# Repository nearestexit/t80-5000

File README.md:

# T80-5000 & T80-5700

[QMK](https://github.com/qmk/qmk_firmware) Compatible Open Hardware USB-C PCBs for the vintage [Cherry G80-5000](https://web.archive.org/web/20250114051116/https://deskthority.net/wiki/Cherry_G80-5000) split ergonomic keyboard and its companion numpad, the G80-5700.

## Overview
The original G80-5000 has two halves which are attached together with a spring, similar to the IBM M15 and the Apple Adjustable Keyboard. They cannot be detached from each other, and the right half must always act as the host.
The original G80-5700 companion numpad can only function when plugged in to the right half of the G80-5000.

This project brings the G80-5000 & 5700 into the 21st century, with all three pieces able to function independently.
There are four PCBs included in this project: the T80-5000 Left, T80-5000 Right, T80-5000 Daughterboard, and T80-5700.
The T80-5000 Left & Right work with QMK's [split keyboard](https://docs.qmk.fm/features/split_keyboard) functionality, and the T80-5700 functions as an independent keyboard which can be passed through the right half's USB hub.

Production files are included for production at [JLCPCB](https://jlcpcb.com/).

## Features
 - USB-C in several configuration options, including internally attached and externally detachable
 - Integrated USB2.0 hub intended for T80-5700 numpad to support passthrough like the original G80-5700
 - [RP2040](https://www.raspberrypi.com/products/rp2040/specifications/) MCU(s) supported by the open-source QMK firmware project

## Supported layouts
 - ISO and ANSI
 - Split backspace
 - 5x4 ortholinear numpad
 - Stepped and centered caps lock

## Configuration options
 - The left and right halves can function independently or in a primary/secondary configuration.
 - The left half's USB-C connector is only accessible internally.
 - The right half's USB-C connector takes advantage of the cutout for the original 5-pin mini DIN to be externally detachable. It is recommended to use the right half as the host.
 - The left and right half can be connected by an internally attached TRRS cable or 4-pin JST-SH cable.
 - The JST-SH cable is small enough to fit through a replacement spring.
 - The daughterboard fits in the right half, leverages the same cutout in the case, and serves as the downstream facing USB-C port for the integrated USB hub. It is connected to the right half with a 4-pin JST-SH cable.
 - The T80-5700 has an internally detachable USB-C connector and functions as an independent USB device.

## JLCPCB Ordering Information
1. On jlcpcb.com, click "order now" and "add gerber file"
2. Navigate to the directory with the gerber.zip - for example, t80-5000-left\jlcpcb\production_files
3. Wait for the gerber to upload.
4. Select the number of PCBs you wish to build.
5. Make sure PCB thickness is set to 1.6mm.
6. Make sure Via covering is set to "tented".
7. Make sure Min via hole size/diameter is set to "0.3mm"
8. For "Mark on PCB" select "Order Number (Specify Position)"
9. Turn the "PCB Assembly" option on
10. Make sure PCBA type is set to "Economic"
11. For "Assembly side", if you are ordering the daughterboard select "top side", otherwise select "bottom side"
12. Click "next", and then "next" again
13. Click "Add BOM File" and select the BOM csv - for example, BOM-T80-5000-left.csv
14. Click "Add CPL File" and select the CPL csv - for example, CPL-T80-5000-left.csv
15. Click "Process BOM and CPL"
16. Make sure all parts are in stock - if any are not in stock, you will need to find replacements
17. If you wish to purchase and solder the TRRS sockets separately (recommended to save money), unselect "J2" in this list
18. **IMPORTANT:** Click "Bottom" to view the bottom side of the PCB, and begin inspecting the component placements. You **WILL** need to correct some component rotations. If you are not sure at this step, do not continue!
19. Click "next" and finish checking out.

When I ordered the V0.1 prototype on 11/8/2024, The total price was $207.63 total for Qty. 5 of all PCBs (left, right, daughterboard, and 5700) plus shipping, or roughly $52.71 per set of Left, Right, Daughterboard, and 5700.

## Additional Components:
- 1x 1:1 ~50mm 4-pin JST-SH cable to connect Left PCB to daughterboard
  - **IMPORTANT:** this must be a 1:1 cable, or else you will short VCC to ground!
  - This means that pin 1 of one connector must be wired to pin 1 of the other connector. If you are unsure, lay the cable flat with no wires crossing - if the connectors on either side are the same way up, it is NOT a 1:1 cable. If they are flipped, it is a 1:1 cable.
  - You can get 1:1 JST-SH cables from many places, but I recommend purchasing a Sparkfun QWIIC starter kit like [this](https://www.amazon.com/dp/B08HQ1VSVL)
- 1x 1:1 ~300mm 4-pin JST-SH cable **OR** TRRS cable to connect Left PCB to Right PCB
  - **IMPORTANT:** do not hotswap these connectors! Plugging or unplugging the TRRS connector with power on will short VCC to ground and potentially damage the MCU.
- 3x LEDs for lock lights
  - The board comes with 300 ohm 1206 package resistors pre-soldered. There are holes to add through-hole resistors if you want to change the resistance.
- ~113 MX-compatible switches (this will vary depending on the layout you choose - my ISO configuration uses 108 switches)
- [PJ-320A](https://www.lcsc.com/product-detail/Audio-Connectors_XKB-Connectivity-PJ-320A_C2884926.html) 3.5mm 4 pin TRRS receptacle (optional) - if you wish to use a TRRS cable and choose not to have it soldered by JLCPCB
- Spring (optional) - An image displaying the approximate measurements of the original spring is included in the documentation folder. I used [these](https://www.amazon.com/dp/B0BRHF1DBL) springs.

## Firmware
- [Vial-QMK](https://get.vial.today/) .uf2 files are provided in the firmware folder.
- To put the keyboard into bootloader mode to flash the firmware:
1. Unplug the USB cable
2. Short the BOOT pins with a pair of tweezers
3. Plug the USB cable in
4. Stop shorting the BOOT pins.
- The RP2040 will then be loaded onto your computer as a USB storage device. Drag in the .uf2 firmware file, and it will reboot.
- The boot pins can be found on the Left side by removing the 1 key, the Right side by removing the 0 key, and the Numpad by removing the * key.
- Once you have flashed the firmware, you can change the keymap from [vial.rocks](https://vial.rocks)

## Other Important Notes
- The components are soldered on to the bottom of this PCB. If you are not careful when putting the keyboard together, you can knock components off the PCB.
- The USB-C receptacles for the right half and the downstream-facing USB hub are close enough together that if the downstream USB-C port is used, cables with thick ends will not work.
- If you do not use the downstream-facing USB-C port, there is no limit to the size of the USB-C cable.
- The USB-Hub will not function if the left side is used as the host.

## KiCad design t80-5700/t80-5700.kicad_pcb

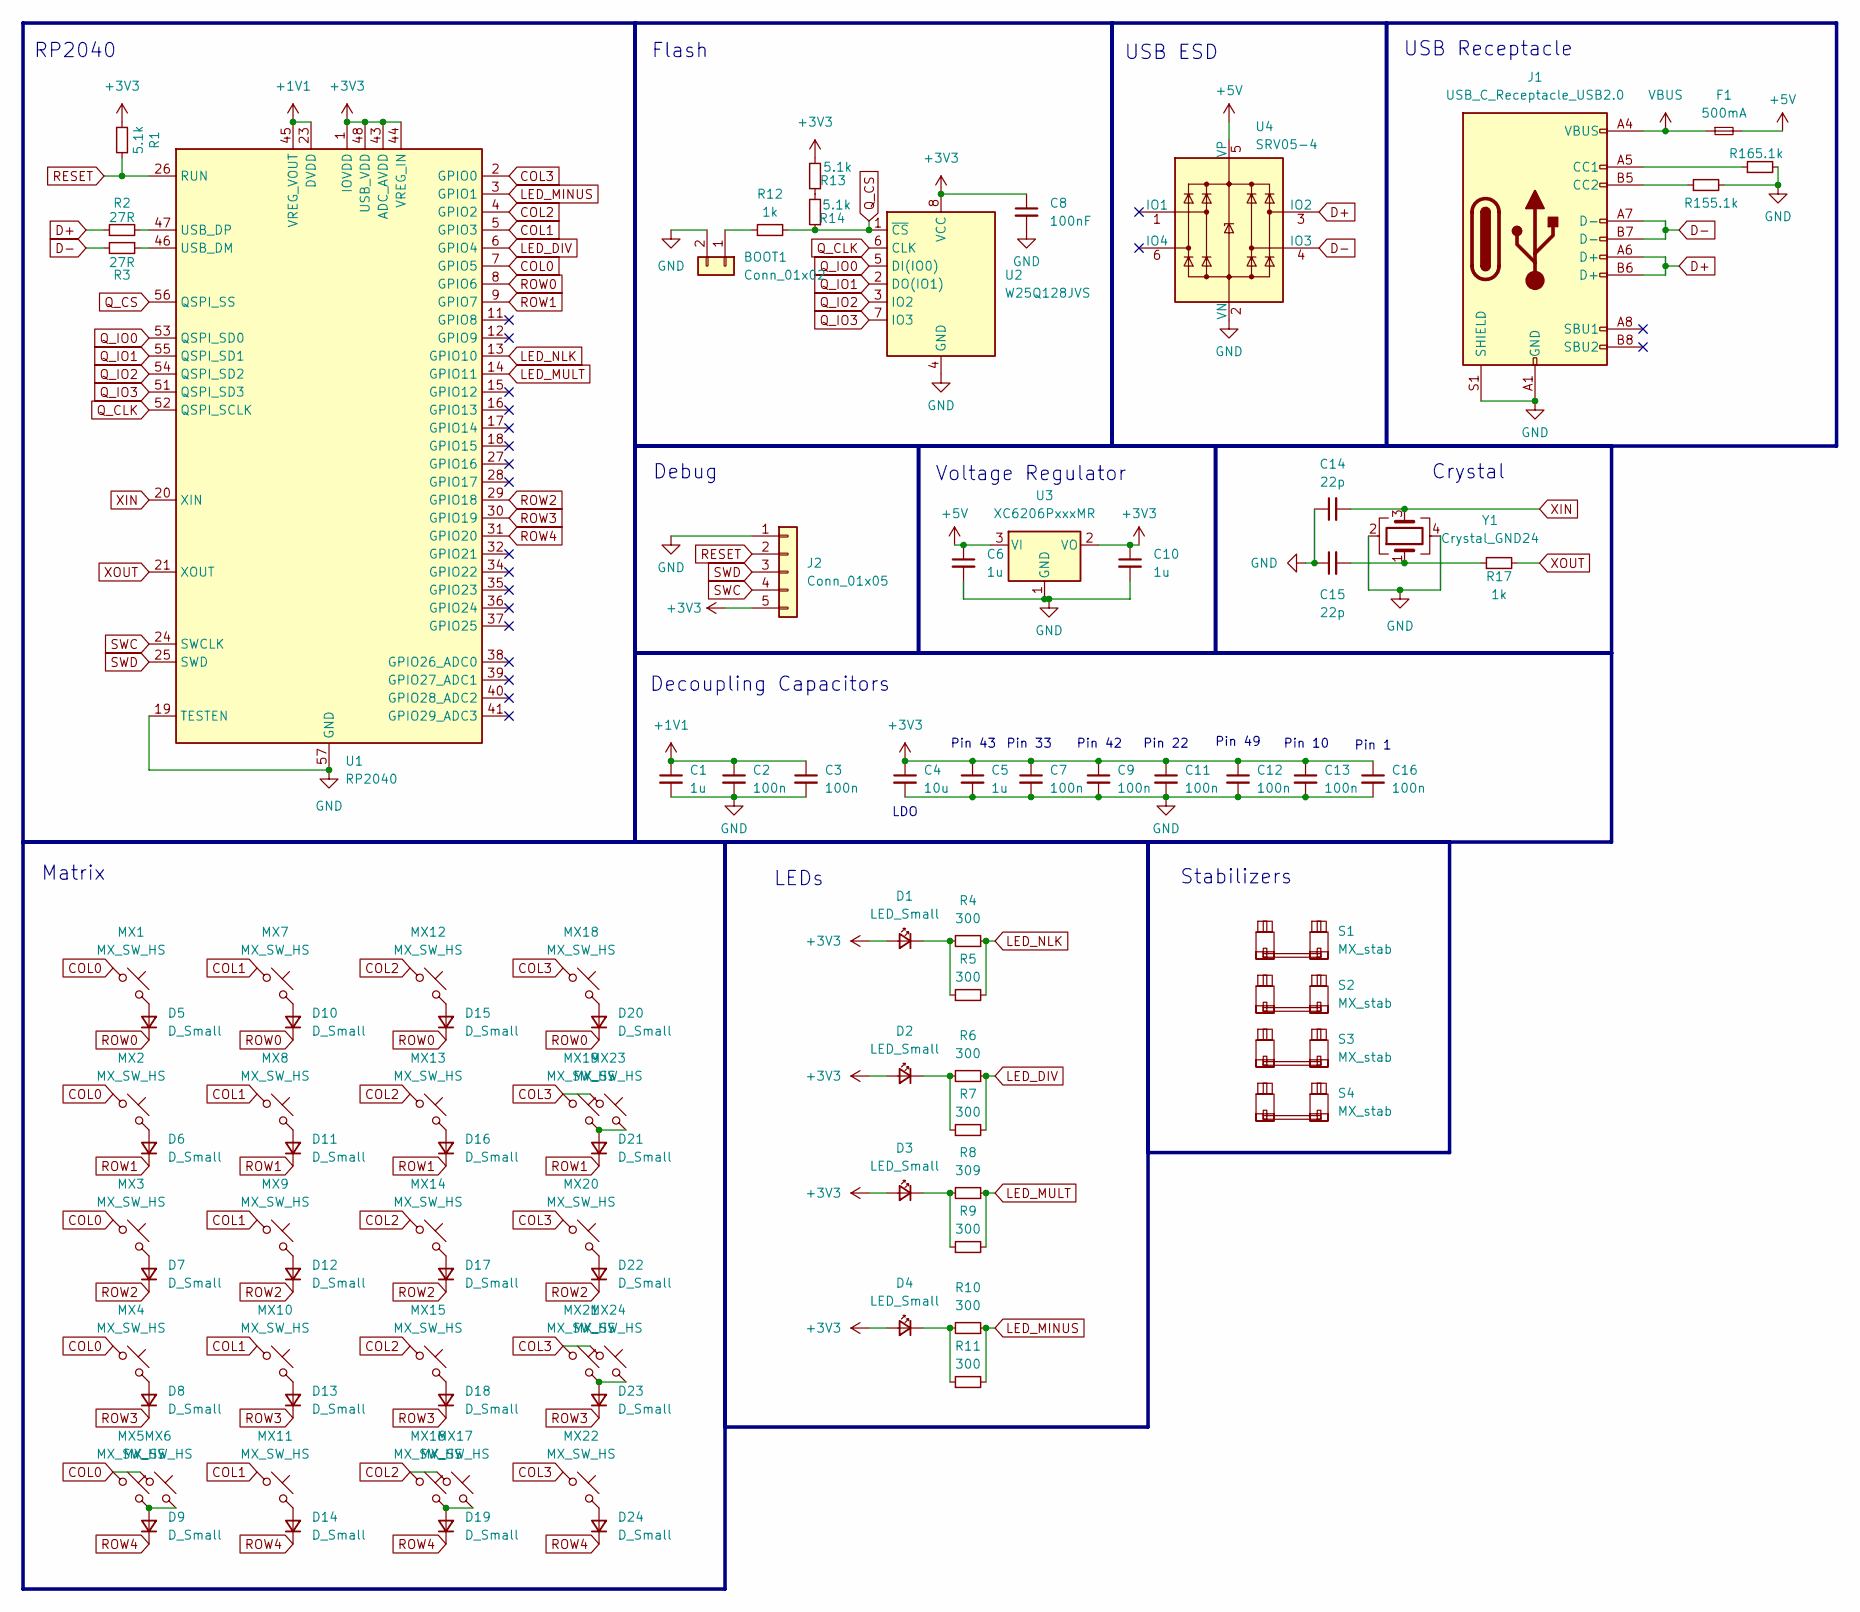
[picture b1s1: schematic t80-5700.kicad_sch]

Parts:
BOOT1: Conn_01x02; PinHeader_1x02_P2.54mm_Vertical
C1, C5, C6, C10: 1u; C_0402_1005Metric
C2, C3, C7, C9, C11, C12, C13, C16: 100n; C_0402_1005Metric
C4: 10u; C_0603_1608Metric
C8: 100nF; C_0402_1005Metric
C14, C15: 22p; C_0402_1005Metric
D1, D2, D3, D4: LED_Small; LED_MX_3mm
D5, D6, D7, D8, D9, D10, D11, D12, D13, D14, D15, D16, D17, D18, D19, D20, D21, D22, D23, D24: D_Small; D_SOD-123-ShiftedSoldermask
F1: 500mA; Fuse_1206_3216Metric
J1: USB_C_Receptacle_USB2.0; USB_C_Receptacle_HRO_TYPE-C-31-M-12
J2: Conn_01x05; PinHeader_1x05_P2.54mm_Vertical
MX1, MX2, MX3, MX4, MX5, MX6, MX7, MX8, MX9, MX10, MX11, MX12, MX13, MX14, MX15, MX16, MX17, MX18, MX19, MX20, MX21, MX22, MX23, MX24: MX_SW_HS; SW_MX_1u
R1: 5.1k; R_0603_1608Metric
R2, R3: 27R; R_0402_1005Metric
R4, R6, R10: 300; R_Axial_DIN0207_L6.3mm_D2.5mm_P10.16mm_Horizontal
R5, R7, R9, R11: 300; R_1206_3216Metric_Pad1.30x1.75mm_HandSolder
R8: 309; R_Axial_DIN0207_L6.3mm_D2.5mm_P10.16mm_Horizontal
R12: 1k; R_0603_1608Metric
R13, R14, R15, R16: 5.1k; R_0402_1005Metric
R17: 1k; R_0402_1005Metric
S1, S2, S3, S4: MX_stab; STAB_MX_P_2u
U1: RP2040; QFN-56-1EP_7x7mm_P0.4mm_EP3.2x3.2mm
U2: W25Q128JVS; SOIC-8_5.23x5.23mm_P1.27mm
U3: XC6206PxxxMR; SOT-23-3
U4: SRV05-4; SOT-23-6-routable
Y1: Crystal_GND24; Crystal_SMD_3225-4Pin_3.2x2.5mm

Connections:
+1V1: C1.1, C2.1, C3.1, U1.23 (DVDD), U1.45 (VREG_VOUT), U1.50 (DVDD)
+3V3: C4.1, C5.1, C7.1, C8.1, C9.1, C10.1, C11.1, C12.1, C13.1, C16.1, D1.2 (A), D2.2 (A), D3.2 (A), D4.2 (A), J2.5, R1.2, R13.2, U1.1 (IOVDD), U1.10 (IOVDD), U1.22 (IOVDD), U1.33 (IOVDD), U1.42 (IOVDD), U1.43 (ADC_AVDD), U1.44 (VREG_IN), U1.48 (USB_VDD), U1.49 (IOVDD), U2.8 (VCC), U3.2 (VO)
+5V: C6.1, F1.2, U3.3 (VI), U4.5 (VP)
COL0: MX1.1, MX2.1, MX3.1, MX4.1, MX5.1, MX6.1, U1.7 (GPIO5)
COL1: MX7.1, MX8.1, MX9.1, MX10.1, MX11.1, U1.5 (GPIO3)
COL2: MX12.1, MX13.1, MX14.1, MX15.1, MX16.1, MX17.1, U1.4 (GPIO2)
COL3: MX18.1, MX19.1, MX20.1, MX21.1, MX22.1, MX23.1, MX24.1, U1.2 (GPIO0)
D+: J1.A6 (D+), J1.B6 (D+), R2.1, U4.3 (IO2)
D-: J1.A7 (D-), J1.B7 (D-), R3.2, U4.4 (IO3)
GND: BOOT1.2, C1.2, C2.2, C3.2, C4.2, C5.2, C6.2, C7.2, C8.2, C9.2, C10.2, C11.2, C12.2, C13.2, C14.1, C15.1, C16.2, J1.A1 (GND), J1.A12 (GND), J1.B1 (GND), J1.B12 (GND), J1.S1 (SHIELD), J2.1, R15.2, R16.2, U1.19 (TESTEN), U1.57 (GND), U2.4 (GND), U3.1 (GND), U4.2 (VN), Y1.2, Y1.4
LED_DIV: R6.1, R7.2, U1.6 (GPIO4)
LED_MINUS: R10.1, R11.2, U1.3 (GPIO1)
LED_MULT: R8.1, R9.2, U1.14 (GPIO11)
LED_NLK: R4.1, R5.2, U1.13 (GPIO10)
unnamed: BOOT1.1, R12.1
unnamed: C15.2, R17.1, Y1.1
unnamed: D1.1 (K), R4.2, R5.1
unnamed: D2.1 (K), R6.2, R7.1
unnamed: D3.1 (K), R8.2, R9.1
unnamed: D4.1 (K), R10.2, R11.1
unnamed: D5.2 (A), MX1.2
unnamed: D6.2 (A), MX2.2
unnamed: D7.2 (A), MX3.2
unnamed: D8.2 (A), MX4.2
unnamed: D9.2 (A), MX5.2, MX6.2
unnamed: D10.2 (A), MX7.2
unnamed: D11.2 (A), MX8.2
unnamed: D12.2 (A), MX9.2
unnamed: D13.2 (A), MX10.2
unnamed: D14.2 (A), MX11.2
unnamed: D15.2 (A), MX12.2
unnamed: D16.2 (A), MX13.2
unnamed: D17.2 (A), MX14.2
unnamed: D18.2 (A), MX15.2
unnamed: D19.2 (A), MX16.2, MX17.2
unnamed: D20.2 (A), MX18.2
unnamed: D21.2 (A), MX19.2, MX23.2
unnamed: D22.2 (A), MX20.2
unnamed: D23.2 (A), MX21.2, MX24.2
unnamed: D24.2 (A), MX22.2
unnamed: J1.A5 (CC1), R16.1
unnamed: J1.B5 (CC2), R15.1
unnamed: R13.1, R14.2
unnamed: R3.1, U1.46 (USB_DM)
unnamed: R2.2, U1.47 (USB_DP)
Q_CLK: U1.52 (QSPI_SCLK), U2.6 (CLK)
Q_CS: R12.2, R14.1, U1.56 (QSPI_SS), U2.1 (~CS)
Q_IO0: U1.53 (QSPI_SD0), U2.5 (DI(IO0))
Q_IO1: U1.55 (QSPI_SD1), U2.2 (DO(IO1))
Q_IO2: U1.54 (QSPI_SD2), U2.3 (IO2)
Q_IO3: U1.51 (QSPI_SD3), U2.7 (IO3)
RESET: J2.2, R1.1, U1.26 (RUN)
ROW0: D5.1 (K), D10.1 (K), D15.1 (K), D20.1 (K), U1.8 (GPIO6)
ROW1: D6.1 (K), D11.1 (K), D16.1 (K), D21.1 (K), U1.9 (GPIO7)
ROW2: D7.1 (K), D12.1 (K), D17.1 (K), D22.1 (K), U1.29 (GPIO18)
ROW3: D8.1 (K), D13.1 (K), D18.1 (K), D23.1 (K), U1.30 (GPIO19)
ROW4: D9.1 (K), D14.1 (K), D19.1 (K), D24.1 (K), U1.31 (GPIO20)
SWC: J2.4, U1.24 (SWCLK)
SWD: J2.3, U1.25 (SWD)
VBUS: F1.1, J1.A4 (VBUS), J1.A9 (VBUS), J1.B4 (VBUS), J1.B9 (VBUS)
XIN: C14.2, U1.20 (XIN), Y1.3
XOUT: R17.2, U1.21 (XOUT)

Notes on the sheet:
Pin 43
LDO
USB ESD
Stabilizers
Crystal
Pin 1
USB Receptacle
Pin 33
Pin 49
Debug
LEDs
Pin 10
Decoupling Capacitors
Flash
Pin 42
RP2040
Voltage Regulator
Matrix
Pin 22

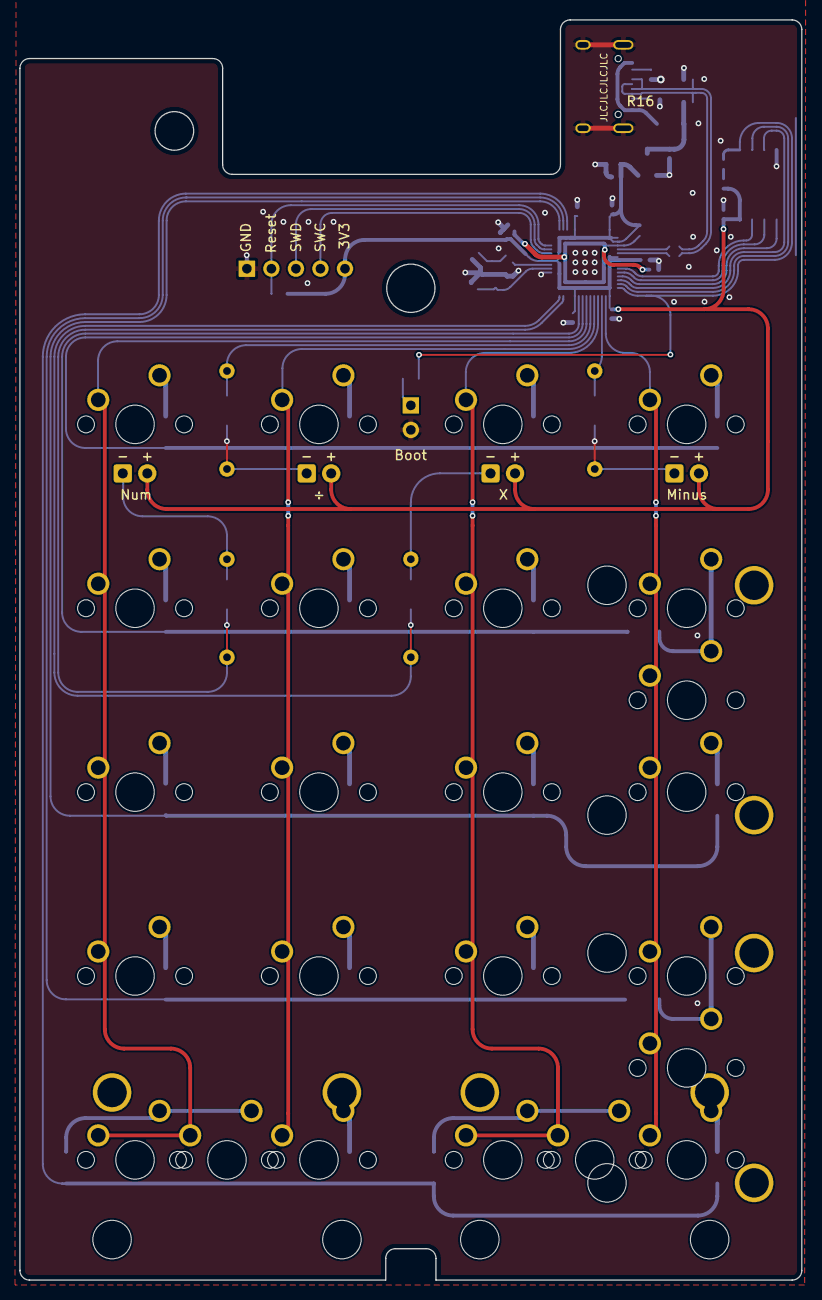
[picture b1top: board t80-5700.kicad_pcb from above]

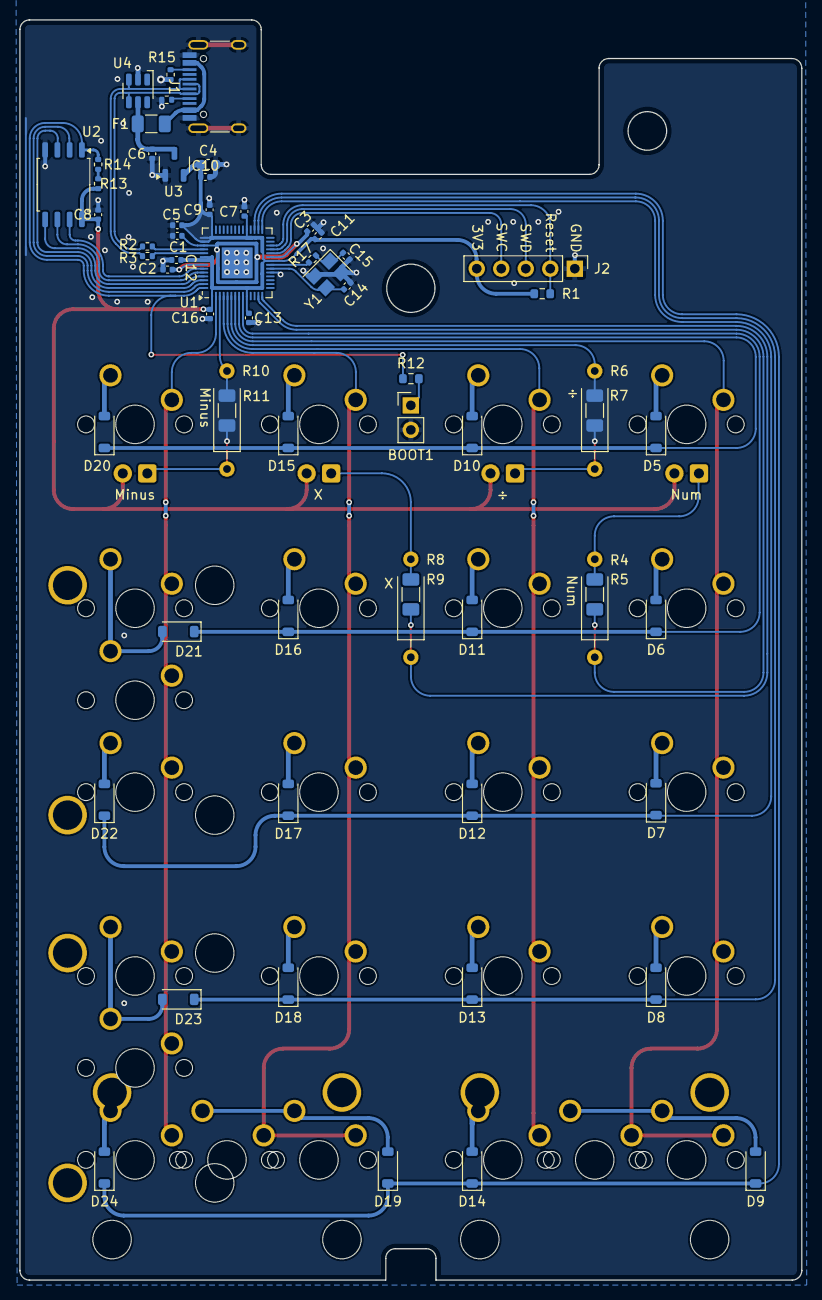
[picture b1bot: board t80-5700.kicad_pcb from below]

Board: 2 copper layers, 81.0 x 130.6 mm, 94 parts (70 on the bottom side), 61 nets.

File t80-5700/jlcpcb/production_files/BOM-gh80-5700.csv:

Comment,Designator,Footprint,LCSC,Quantity
1k,R17,R_0402_1005Metric,C11702,1
W25Q128JVS,U2,SOIC-8_5.23x5.23mm_P1.27mm,C131025,1
27R,"R2,R3",R_0402_1005Metric,C138021,2
22p,"C14,C15",C_0402_1005Metric,C1555,2
USB_C_Receptacle_USB2.0,J1,USB_C_Receptacle_HRO_TYPE-C-31-M-12,C165948,1
300,"R11,R5,R7,R9",R_1206_3216Metric_Pad1.30x1.75mm_HandSolder,C17887,4
10u,C4,C_0603_1608Metric,C19702,1
RP2040,U1,QFN-56-1EP_7x7mm_P0.4mm_EP3.2x3.2mm,C2040,1
1k,R12,R_0603_1608Metric,C21190,1
5.1k,R1,R_0603_1608Metric,C23186,1
5.1k,"R13,R14,R15,R16",R_0402_1005Metric,C25905,4
100n,"C11,C12,C13,C16,C2,C3,C7,C8,C9",C_0402_1005Metric,C307331,9
1u,"C1,C10,C5,C6",C_0402_1005Metric,C52923,4
XC6206PxxxMR,U3,SOT-23-3,C5446,1
500mA,F1,Fuse_1206_3216Metric,C70076,1
D_Small,"D10,D11,D12,D13,D14,D15,D16,D17,D18,D19,D20,D21,D22,D23,D24,D5,D6,D7,D8,D9",D_SOD-123-ShiftedSoldermask,C81598,20
SRV05-4,U4,SOT-23-6-routable,C85364,1
Crystal_GND24,Y1,Crystal_SMD_3225-4Pin_3.2x2.5mm,C9002,1

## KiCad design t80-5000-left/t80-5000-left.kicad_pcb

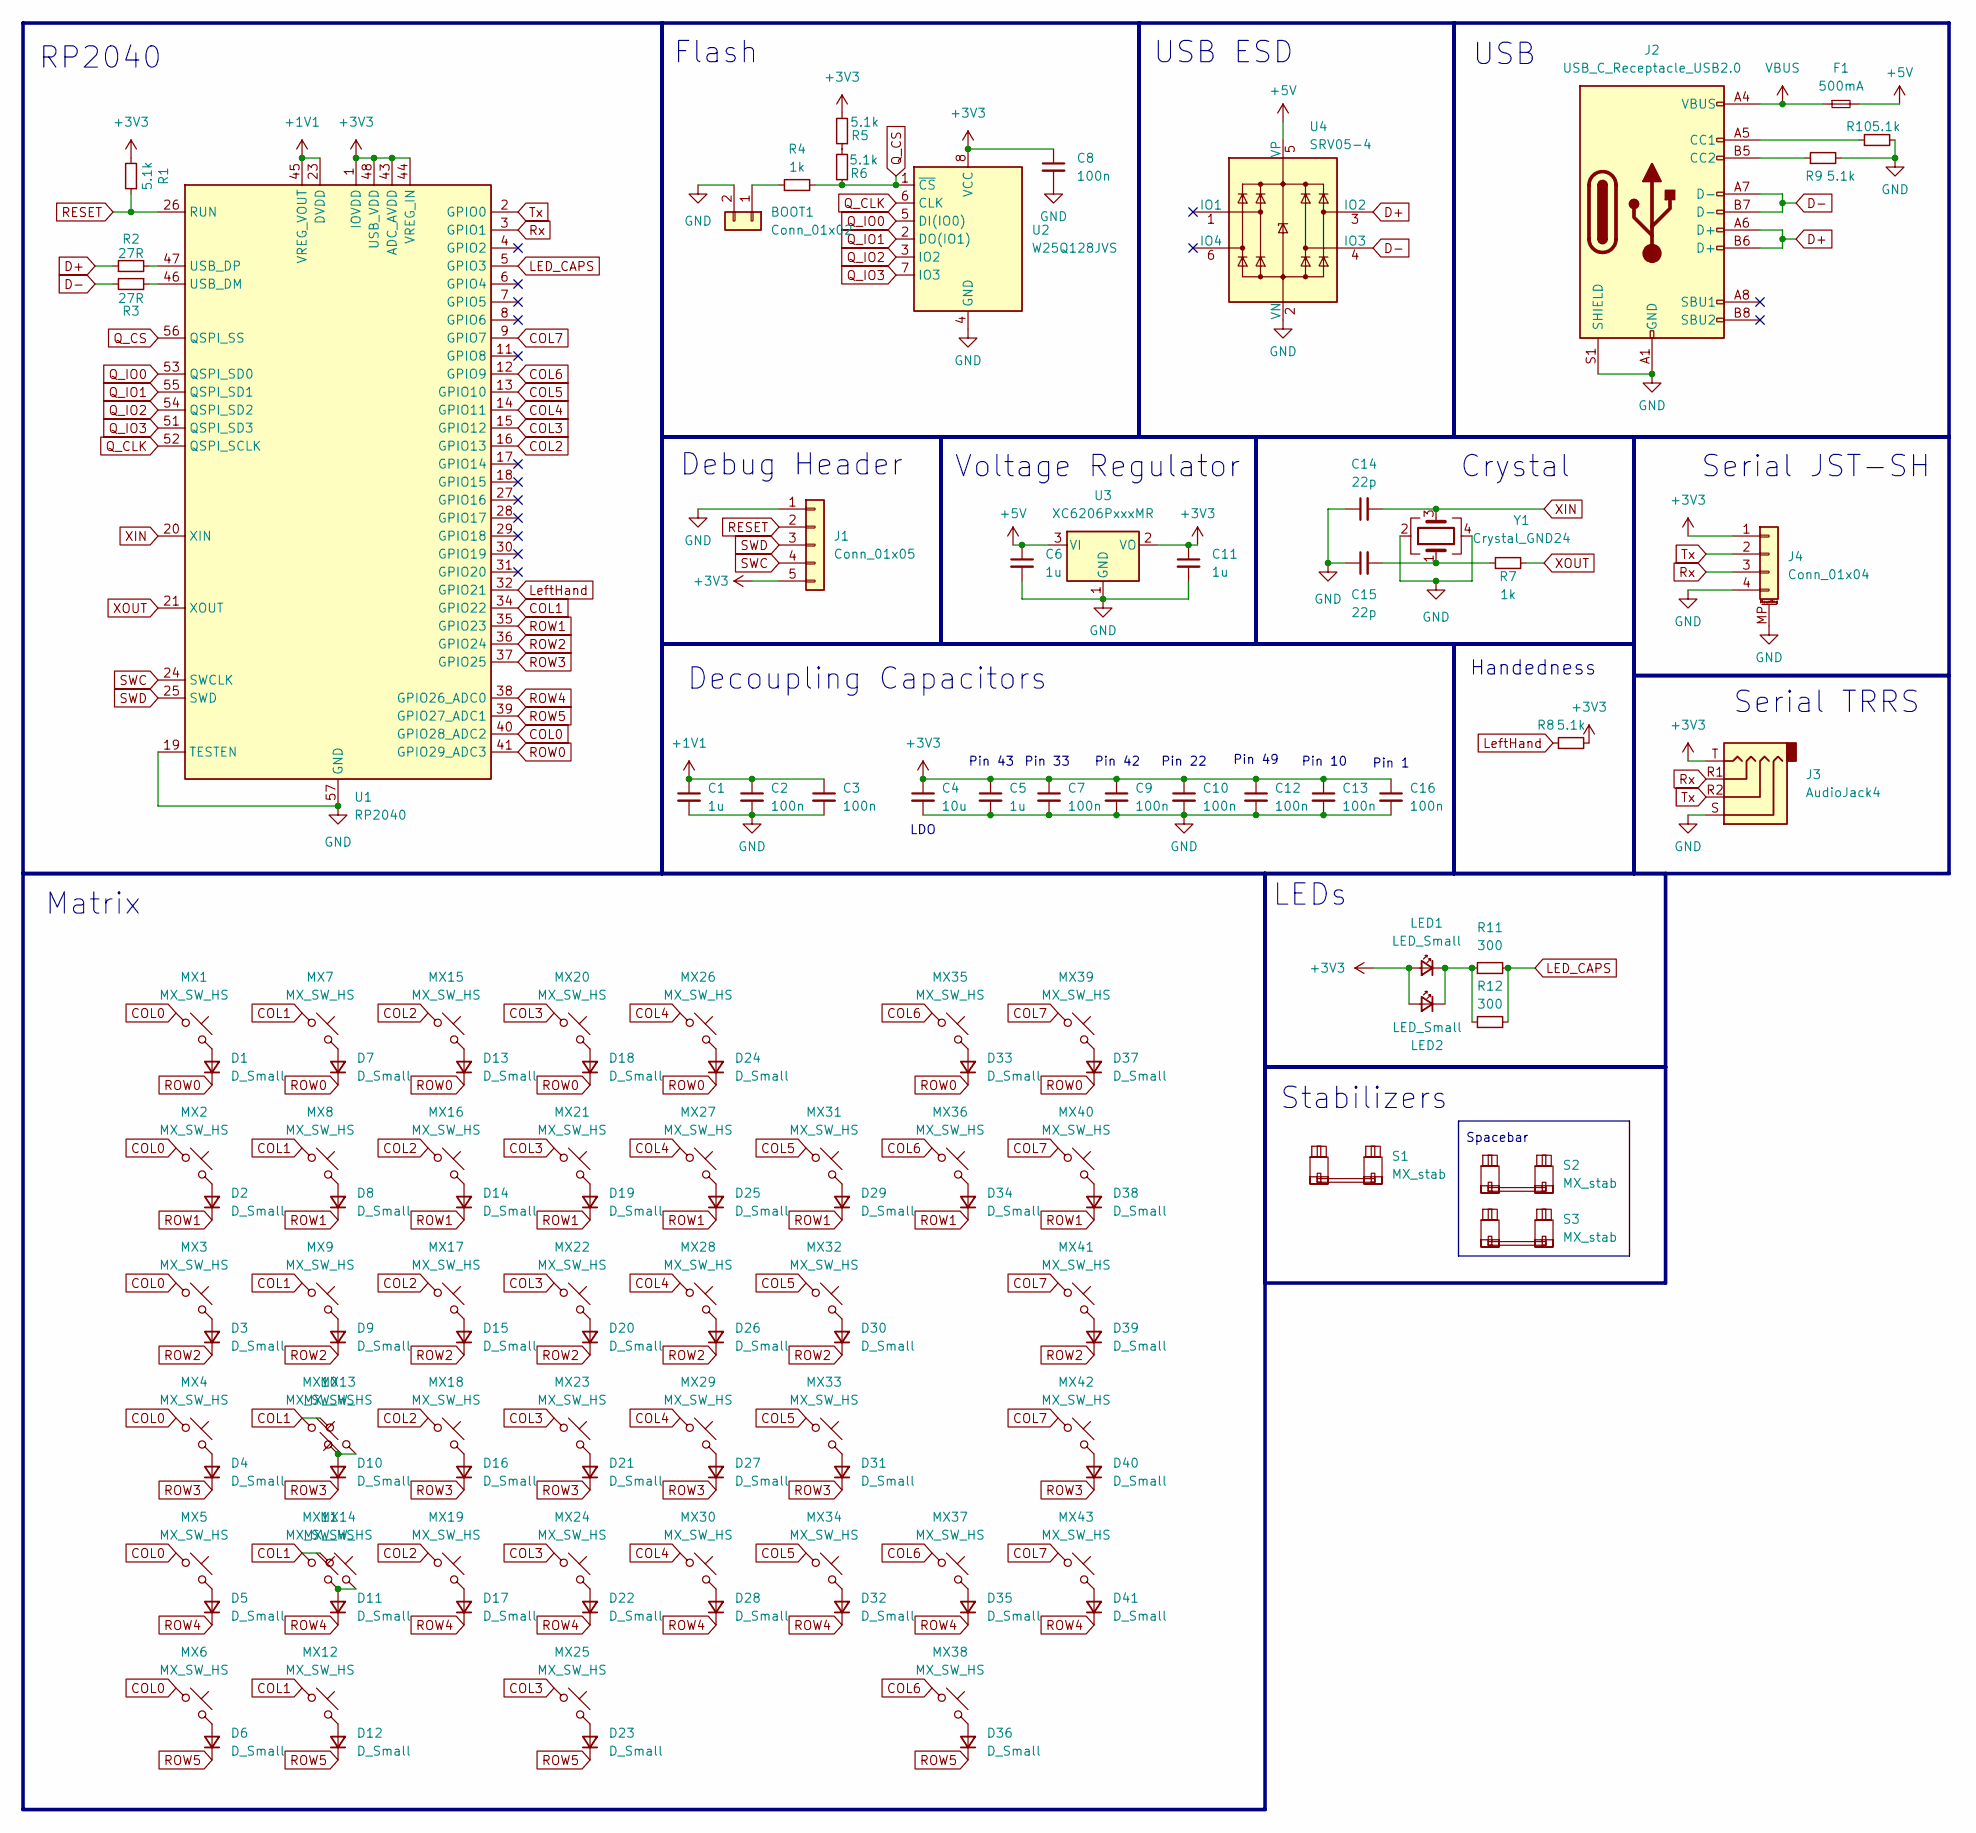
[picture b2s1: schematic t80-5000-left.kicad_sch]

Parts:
BOOT1: Conn_01x02; PinHeader_1x02_P2.54mm_Vertical
C1, C5, C6, C11: 1u; C_0402_1005Metric
C2, C3, C7, C8, C9, C10, C12, C13, C16: 100n; C_0402_1005Metric
C4: 10u; C_0603_1608Metric
C14, C15: 22p; C_0402_1005Metric
D1, D2, D3, D4, D5, D6, D7, D8, D9, D10, D11, D12, D13, D14, D15, D16, D17, D18, D19, D20, D21, D22, D23, D24, D25, D26, D27, D28, D29, D30, D31, D32, D33, D34, D35, D36, D37, D38, D39, D40, D41: D_Small; D_SOD-123-ShiftedSoldermask
F1: 500mA; Fuse_1206_3216Metric
J1: Conn_01x05; PinHeader_1x05_P2.54mm_Vertical
J2: USB_C_Receptacle_USB2.0; USB_C_Receptacle_HRO_TYPE-C-31-M-12
J3: AudioJack4; AUDIO-TH_XKB_PJ-320A
J4: Conn_01x04; JST_SH_SM04B-SRSS-TB_1x04-1MP_P1.00mm_Horizontal
LED1, LED2: LED_Small; LED_MX_3mm
MX1, MX2, MX3, MX4, MX5, MX6, MX7, MX8, MX9, MX10, MX11, MX12, MX13, MX14, MX15, MX16, MX17, MX18, MX19, MX20, MX21, MX22, MX23, MX24, MX25, MX26, MX27, MX28, MX29, MX30, MX31, MX32, MX33, MX34, MX35, MX36, MX37, MX38, MX39, MX40, MX41, MX42, MX43: MX_SW_HS; SW_MX_1u
R1, R5, R6, R9, R10: 5.1k; R_0402_1005Metric
R2, R3: 27R; R_0402_1005Metric
R4, R7: 1k; R_0402_1005Metric
R8: 5.1k; R_0603_1608Metric_Pad0.98x0.95mm_HandSolder
R11: 300; R_Axial_DIN0207_L6.3mm_D2.5mm_P10.16mm_Horizontal
R12: 300; R_1206_3216Metric_Pad1.30x1.75mm_HandSolder
S1: MX_stab; STAB_MX_P_2u
S2: MX_stab; STAB_MX_3.5u_5000
S3: MX_stab; STAB_MX_5000
U1: RP2040; QFN-56-1EP_7x7mm_P0.4mm_EP3.2x3.2mm
U2: W25Q128JVS; SOIC-8_5.23x5.23mm_P1.27mm
U3: XC6206PxxxMR; SOT-23-3
U4: SRV05-4; SOT-23-6-routable
Y1: Crystal_GND24; Crystal_SMD_3225-4Pin_3.2x2.5mm

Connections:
+1V1: C1.1, C2.1, C3.1, U1.23 (DVDD), U1.45 (VREG_VOUT), U1.50 (DVDD)
+3V3: C4.1, C5.1, C7.1, C8.1, C9.1, C10.1, C11.1, C12.1, C13.1, C16.1, J1.5, J3.T, J4.1, LED1.2 (A), LED2.2 (A), R1.2, R5.2, R8.2, U1.1 (IOVDD), U1.10 (IOVDD), U1.22 (IOVDD), U1.33 (IOVDD), U1.42 (IOVDD), U1.43 (ADC_AVDD), U1.44 (VREG_IN), U1.48 (USB_VDD), U1.49 (IOVDD), U2.8 (VCC), U3.2 (VO)
+5V: C6.1, F1.2, U3.3 (VI), U4.5 (VP)
COL0: MX1.1, MX2.1, MX3.1, MX4.1, MX5.1, MX6.1, U1.40 (GPIO28_ADC2)
COL1: MX7.1, MX8.1, MX9.1, MX10.1, MX11.1, MX12.1, MX13.2, MX14.1, U1.34 (GPIO22)
COL2: MX15.1, MX16.1, MX17.1, MX18.1, MX19.1, U1.16 (GPIO13)
COL3: MX20.1, MX21.1, MX22.1, MX23.1, MX24.1, MX25.1, U1.15 (GPIO12)
COL4: MX26.1, MX27.1, MX28.1, MX29.1, MX30.1, U1.14 (GPIO11)
COL5: MX31.1, MX32.1, MX33.1, MX34.1, U1.13 (GPIO10)
COL6: MX35.1, MX36.1, MX37.1, MX38.1, U1.12 (GPIO9)
COL7: MX39.1, MX40.1, MX41.1, MX42.1, MX43.1, U1.9 (GPIO7)
D+: J2.A6 (D+), J2.B6 (D+), R2.1, U4.3 (IO2)
D-: J2.A7 (D-), J2.B7 (D-), R3.2, U4.4 (IO3)
GND: BOOT1.2, C1.2, C2.2, C3.2, C4.2, C5.2, C6.2, C7.2, C8.2, C9.2, C10.2, C11.2, C12.2, C13.2, C14.1, C15.1, C16.2, J1.1, J2.A1 (GND), J2.A12 (GND), J2.B1 (GND), J2.B12 (GND), J2.S1 (SHIELD), J3.S, J4.4, J4.MP (MountPin), R9.2, R10.2, U1.19 (TESTEN), U1.57 (GND), U2.4 (GND), U3.1 (GND), U4.2 (VN), Y1.2, Y1.4
LED_CAPS: R11.2, R12.2, U1.5 (GPIO3)
LeftHand: R8.1, U1.32 (GPIO21)
unnamed: BOOT1.1, R4.1
unnamed: C15.2, R7.1, Y1.1
unnamed: D1.2 (A), MX1.2
unnamed: D2.2 (A), MX2.2
unnamed: D3.2 (A), MX3.2
unnamed: D4.2 (A), MX4.2
unnamed: D5.2 (A), MX5.2
unnamed: D6.2 (A), MX6.2
unnamed: D7.2 (A), MX7.2
unnamed: D8.2 (A), MX8.2
unnamed: D9.2 (A), MX9.2
unnamed: D10.2 (A), MX10.2, MX13.1
unnamed: D11.2 (A), MX11.2, MX14.2
unnamed: D12.2 (A), MX12.2
unnamed: D13.2 (A), MX15.2
unnamed: D14.2 (A), MX16.2
unnamed: D15.2 (A), MX17.2
unnamed: D16.2 (A), MX18.2
unnamed: D17.2 (A), MX19.2
unnamed: D18.2 (A), MX20.2
unnamed: D19.2 (A), MX21.2
unnamed: D20.2 (A), MX22.2
unnamed: D21.2 (A), MX23.2
unnamed: D22.2 (A), MX24.2
unnamed: D23.2 (A), MX25.2
unnamed: D24.2 (A), MX26.2
unnamed: D25.2 (A), MX27.2
unnamed: D26.2 (A), MX28.2
unnamed: D27.2 (A), MX29.2
unnamed: D28.2 (A), MX30.2
unnamed: D29.2 (A), MX31.2
unnamed: D30.2 (A), MX32.2
unnamed: D31.2 (A), MX33.2
unnamed: D32.2 (A), MX34.2
unnamed: D33.2 (A), MX35.2
unnamed: D34.2 (A), MX36.2
unnamed: D35.2 (A), MX37.2
unnamed: D36.2 (A), MX38.2
unnamed: D37.2 (A), MX39.2
unnamed: D38.2 (A), MX40.2
unnamed: D39.2 (A), MX41.2
unnamed: D40.2 (A), MX42.2
unnamed: D41.2 (A), MX43.2
unnamed: J2.A5 (CC1), R10.1
unnamed: J2.B5 (CC2), R9.1
unnamed: LED1.1 (K), LED2.1 (K), R11.1, R12.1
unnamed: R5.1, R6.2
unnamed: R3.1, U1.46 (USB_DM)
unnamed: R2.2, U1.47 (USB_DP)
Q_CLK: U1.52 (QSPI_SCLK), U2.6 (CLK)
Q_CS: R4.2, R6.1, U1.56 (QSPI_SS), U2.1 (~CS)
Q_IO0: U1.53 (QSPI_SD0), U2.5 (DI(IO0))
Q_IO1: U1.55 (QSPI_SD1), U2.2 (DO(IO1))
Q_IO2: U1.54 (QSPI_SD2), U2.3 (IO2)
Q_IO3: U1.51 (QSPI_SD3), U2.7 (IO3)
RESET: J1.2, R1.1, U1.26 (RUN)
ROW0: D1.1 (K), D7.1 (K), D13.1 (K), D18.1 (K), D24.1 (K), D33.1 (K), D37.1 (K), U1.41 (GPIO29_ADC3)
ROW1: D2.1 (K), D8.1 (K), D14.1 (K), D19.1 (K), D25.1 (K), D29.1 (K), D34.1 (K), D38.1 (K), U1.35 (GPIO23)
ROW2: D3.1 (K), D9.1 (K), D15.1 (K), D20.1 (K), D26.1 (K), D30.1 (K), D39.1 (K), U1.36 (GPIO24)
ROW3: D4.1 (K), D10.1 (K), D16.1 (K), D21.1 (K), D27.1 (K), D31.1 (K), D40.1 (K), U1.37 (GPIO25)
ROW4: D5.1 (K), D11.1 (K), D17.1 (K), D22.1 (K), D28.1 (K), D32.1 (K), D35.1 (K), D41.1 (K), U1.38 (GPIO26_ADC0)
ROW5: D6.1 (K), D12.1 (K), D23.1 (K), D36.1 (K), U1.39 (GPIO27_ADC1)
Rx: J3.R1, J4.3, U1.3 (GPIO1)
SWC: J1.4, U1.24 (SWCLK)
SWD: J1.3, U1.25 (SWD)
Tx: J3.R2, J4.2, U1.2 (GPIO0)
VBUS: F1.1, J2.A4 (VBUS), J2.A9 (VBUS), J2.B4 (VBUS), J2.B9 (VBUS)
XIN: C14.2, U1.20 (XIN), Y1.3
XOUT: R7.2, U1.21 (XOUT)

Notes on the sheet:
Decoupling Capacitors
Debug Header
LDO
Stabilizers
Pin 42
RP2040
Pin 10
Handedness
USB
Voltage Regulator
Flash
Serial JST-SH
LEDs
Crystal
USB ESD
Spacebar
Pin 1
Pin 49
Pin 22
Pin 33
Serial TRRS
Matrix
Pin 43

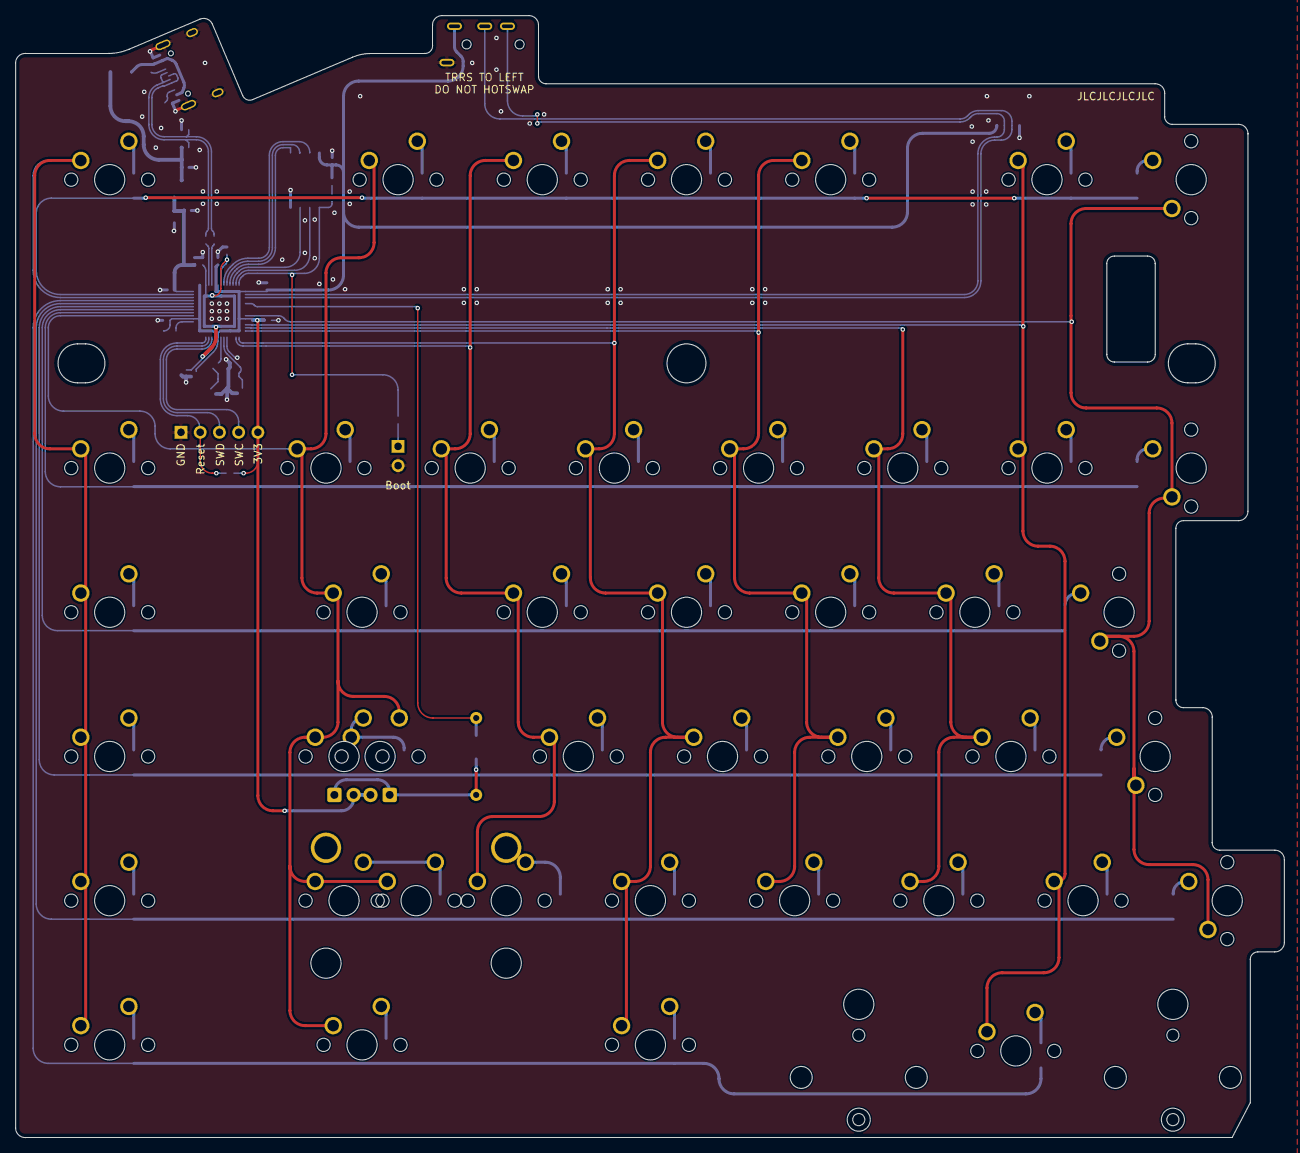
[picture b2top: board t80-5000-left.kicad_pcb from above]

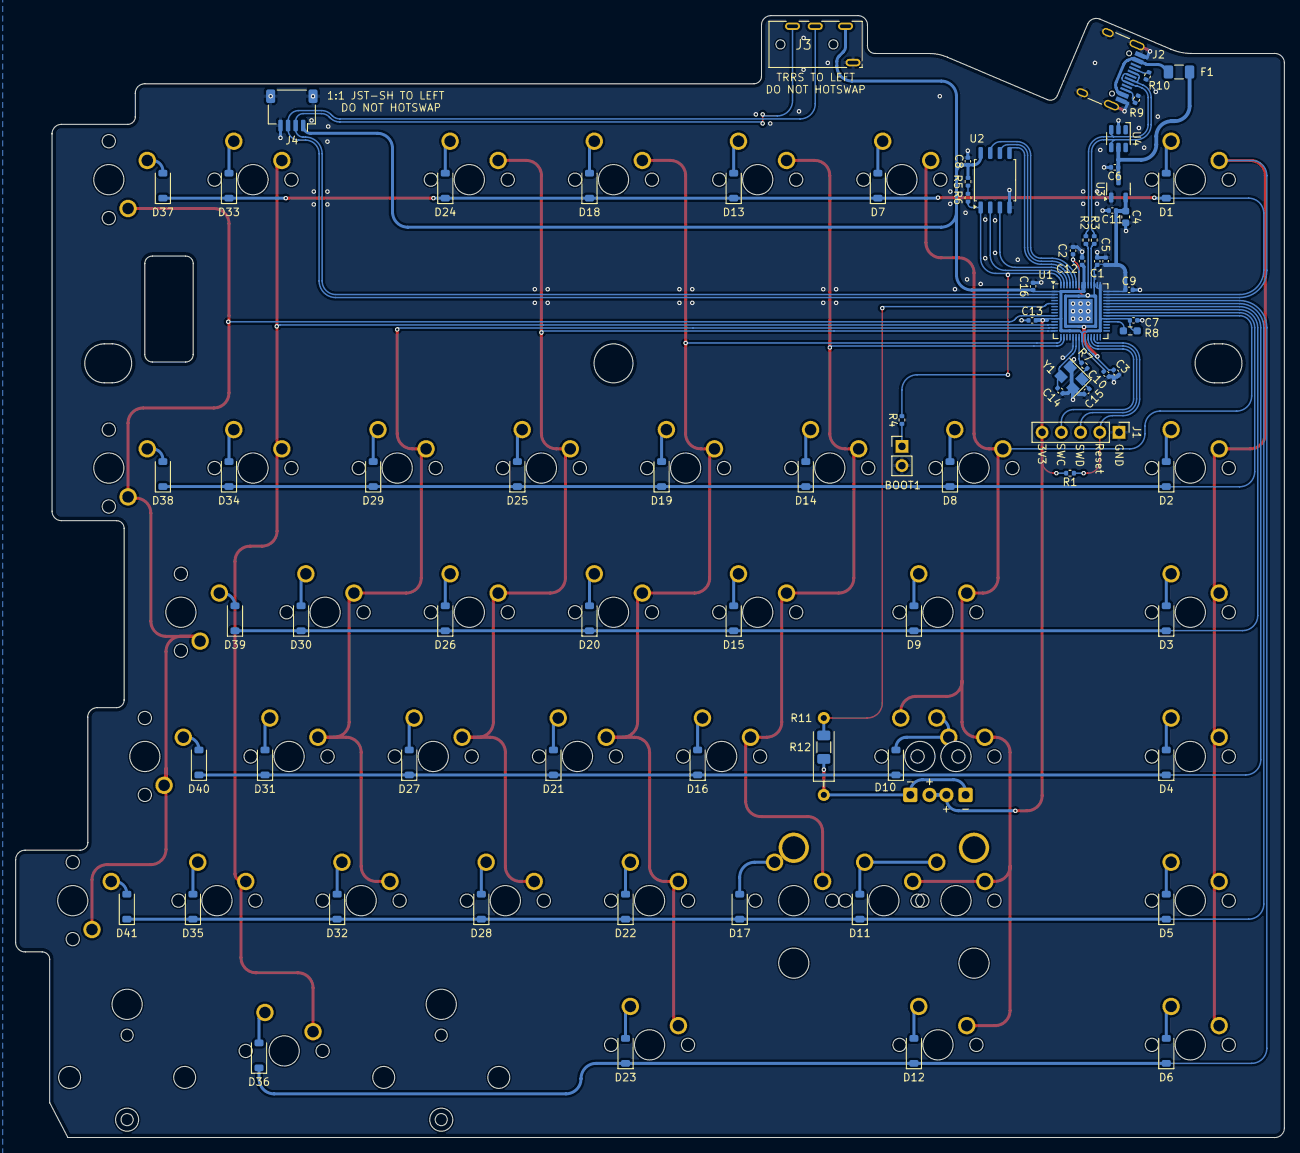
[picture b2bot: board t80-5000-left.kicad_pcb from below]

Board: 2 copper layers, 167.6 x 148.2 mm, 128 parts (80 on the bottom side), 85 nets.

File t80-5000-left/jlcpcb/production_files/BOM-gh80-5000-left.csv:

Comment,Designator,Footprint,LCSC,Quantity
1k,"R4,R7",R_0402_1005Metric,C11702,2
W25Q128JVS,U2,SOIC-8_5.23x5.23mm_P1.27mm,C131025,1
27R,"R2,R3",R_0402_1005Metric,C138021,2
22p,"C14,C15",C_0402_1005Metric,C1555,2
USB_C_Receptacle_USB2.0,J2,USB_C_Receptacle_HRO_TYPE-C-31-M-12,C165948,1
300,R12,R_1206_3216Metric_Pad1.30x1.75mm_HandSolder,C17887,1
10u,C4,C_0603_1608Metric,C19702,1
RP2040,U1,QFN-56-1EP_7x7mm_P0.4mm_EP3.2x3.2mm,C2040,1
5.1k,R8,R_0603_1608Metric_Pad0.98x0.95mm_HandSolder,C23186,1
5.1k,"R1,R10,R5,R6,R9",R_0402_1005Metric,C25905,5
AudioJack4,J3,AUDIO-TH_XKB_PJ-320A,C2884926,1
100n,"C10,C12,C13,C16,C2,C3,C7,C8,C9",C_0402_1005Metric,C307331,9
Conn_01x04,J4,JST_SH_SM04B-SRSS-TB_1x04-1MP_P1.00mm_Horizontal,C371571,1
1u,"C1,C11,C5,C6",C_0402_1005Metric,C52923,4
XC6206PxxxMR,U3,SOT-23-3,C5446,1
500mA,F1,Fuse_1206_3216Metric,C70076,1
D_Small,"D1,D10,D11,D12,D13,D14,D15,D16,D17,D18,D19,D2,D20,D21,D22,D23,D24,D25,D26,D27,D28,D29,D3,D30,D31,D32,D33,D34,D35,D36,D37,D38,D39,D4,D40,D41,D5,D6,D7,D8,D9",D_SOD-123-ShiftedSoldermask,C81598,41
SRV05-4,U4,SOT-23-6-routable,C85364,1
Crystal_GND24,Y1,Crystal_SMD_3225-4Pin_3.2x2.5mm,C9002,1

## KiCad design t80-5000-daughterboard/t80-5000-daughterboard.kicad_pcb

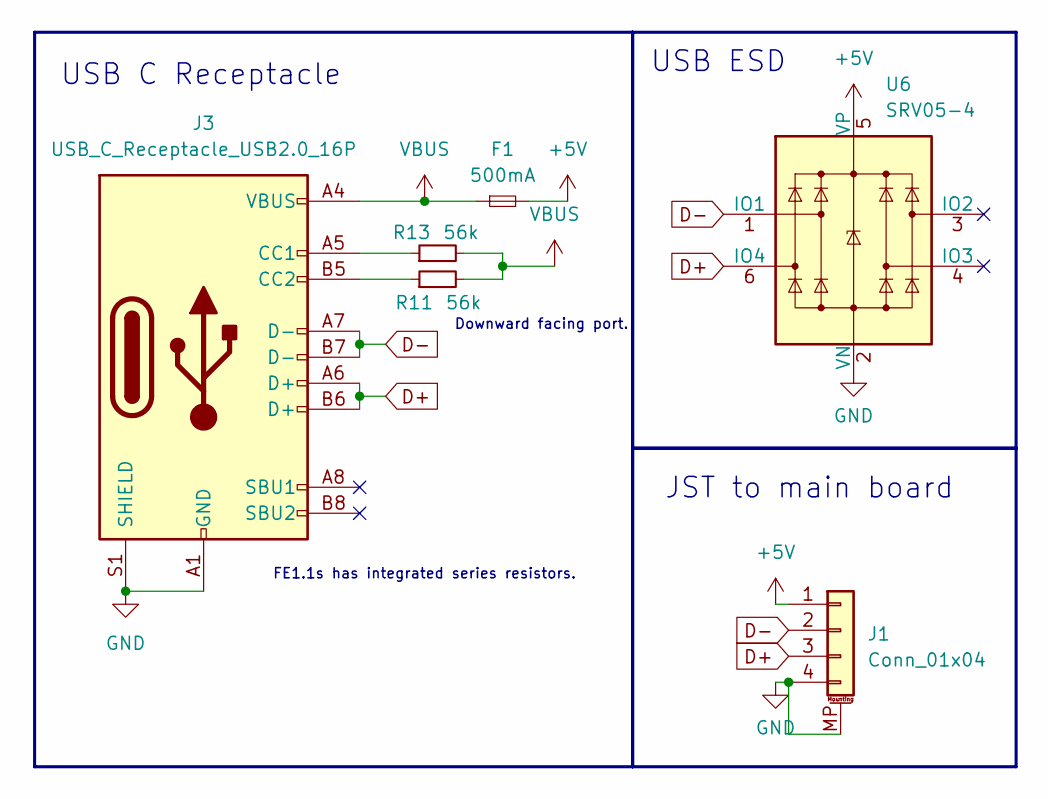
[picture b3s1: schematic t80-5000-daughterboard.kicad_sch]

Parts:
F1: 500mA; Fuse_1206_3216Metric
J1: Conn_01x04; JST_SH_SM04B-SRSS-TB_1x04-1MP_P1.00mm_Horizontal
J3: USB_C_Receptacle_USB2.0_16P; USB-C-SMD_HANBO_MC-121-L119
R11, R13: 56k; R_0402_1005Metric
U6: SRV05-4; SOT-23-6-routable

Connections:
+5V: F1.2, J1.1, U6.5 (VP)
D+: J1.3, J3.A6 (D+), J3.B6 (D+), U6.6 (IO4)
D-: J1.2, J3.A7 (D-), J3.B7 (D-), U6.1 (IO1)
GND: J1.4, J1.MP (MountPin), J3.A1 (GND), J3.A12 (GND), J3.B1 (GND), J3.B12 (GND), J3.S1 (SHIELD), U6.2 (VN)
unnamed: J3.A5 (CC1), R13.1
unnamed: J3.B5 (CC2), R11.1
VBUS: F1.1, J3.A4 (VBUS), J3.A9 (VBUS), J3.B4 (VBUS), J3.B9 (VBUS), R11.2, R13.2

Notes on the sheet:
FE1.1s has integrated series resistors.
Downward facing port.
JST to main board
USB C Receptacle
USB ESD
